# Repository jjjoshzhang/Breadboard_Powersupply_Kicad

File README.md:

# Breadboard_Powersupply_Kicad
Breadboard Power Supply (LM7805 + LM317) — KiCad Project

A compact, dual-output breadboard power supply module designed between June. 2025 – July. 2025 
This board provides regulated 5 V and adjustable 3.3 V outputs using classic linear regulators (LM7805 and LM317), optimized for prototyping and educational use.

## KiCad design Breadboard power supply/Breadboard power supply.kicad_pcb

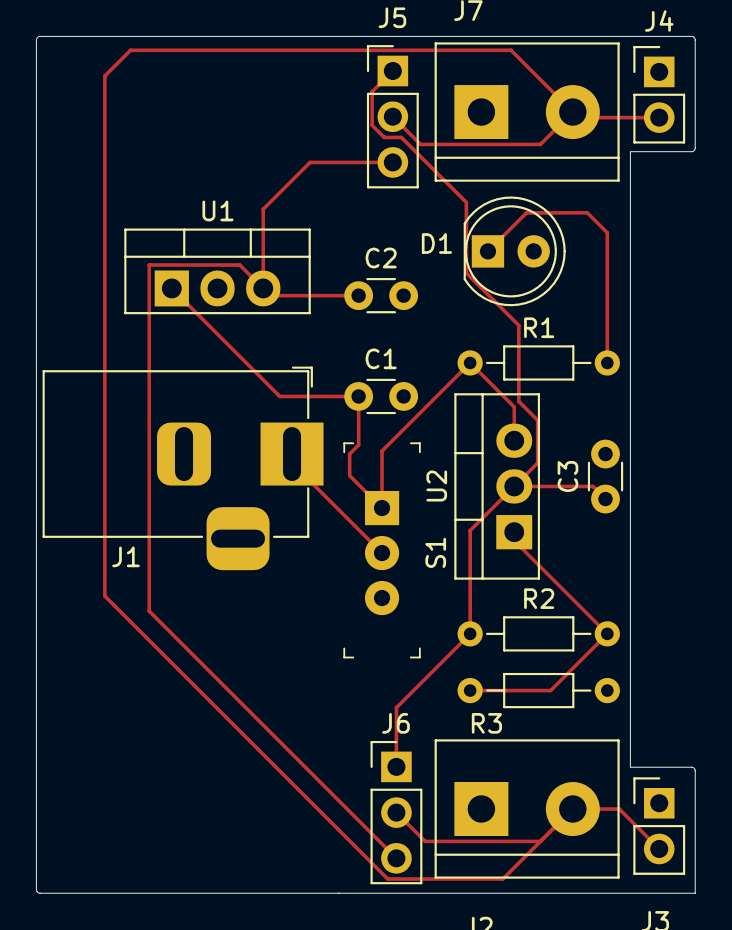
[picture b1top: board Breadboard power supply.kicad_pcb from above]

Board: 2 copper layers, 36.6 x 47.6 mm, 17 parts (0 on the bottom side), 8 nets.

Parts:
C1: 10u; C_Disc_D3.0mm_W1.6mm_P2.50mm
C2: 0.1u; C_Disc_D3.0mm_W1.6mm_P2.50mm
C3: 1u; C_Disc_D3.0mm_W1.6mm_P2.50mm
D1: LED; LED_D5.0mm_Clear
J1: Barrel_Jack_Switch; BarrelJack_Horizontal
J2, J7: Screw_Terminal_01x02; TerminalBlock_bornier-2_P5.08mm
J3, J4: Conn_01x02_Pin; PinHeader_1x02_P2.54mm_Vertical
J5, J6: Conn_01x03_Pin; PinHeader_1x03_P2.54mm_Vertical
R1, R2: 330; R_Axial_DIN0204_L3.6mm_D1.6mm_P7.62mm_Horizontal
R3: 560; R_Axial_DIN0204_L3.6mm_D1.6mm_P7.62mm_Horizontal
S1: EG1218; Switch_Slide_11.6x4mm_EG1218
U1: LM7805_TO220; TO-220-3_Vertical
U2: LM317_TO-220; TO-220-3_Vertical

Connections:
/3.3V: C3.1, J5.1, J6.1, R2.1, U2.2 (VO)
/5V: C2.1, J5.3, J6.3, U1.3 (VO)
/12V: C1.1, R1.1, S1.1, U1.1 (VI), U2.3 (VI)
/PWR_intput: J1.1, S1.2
/PWR_output: J2.2, J3.2, J4.2, J5.2, J6.2, J7.2
GND: C1.2, C2.2, C3.2, D1.2 (A), J1.2, J1.3, J2.1, J3.1, J4.1, J7.1, R3.2, U1.2 (GND)
unnamed: D1.1 (K), R1.2
unnamed: R2.2, R3.1, U2.1 (ADJ)

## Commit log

2025-11-24 Enhance README with project description and details
    Added project description and details for the breadboard power supply.
